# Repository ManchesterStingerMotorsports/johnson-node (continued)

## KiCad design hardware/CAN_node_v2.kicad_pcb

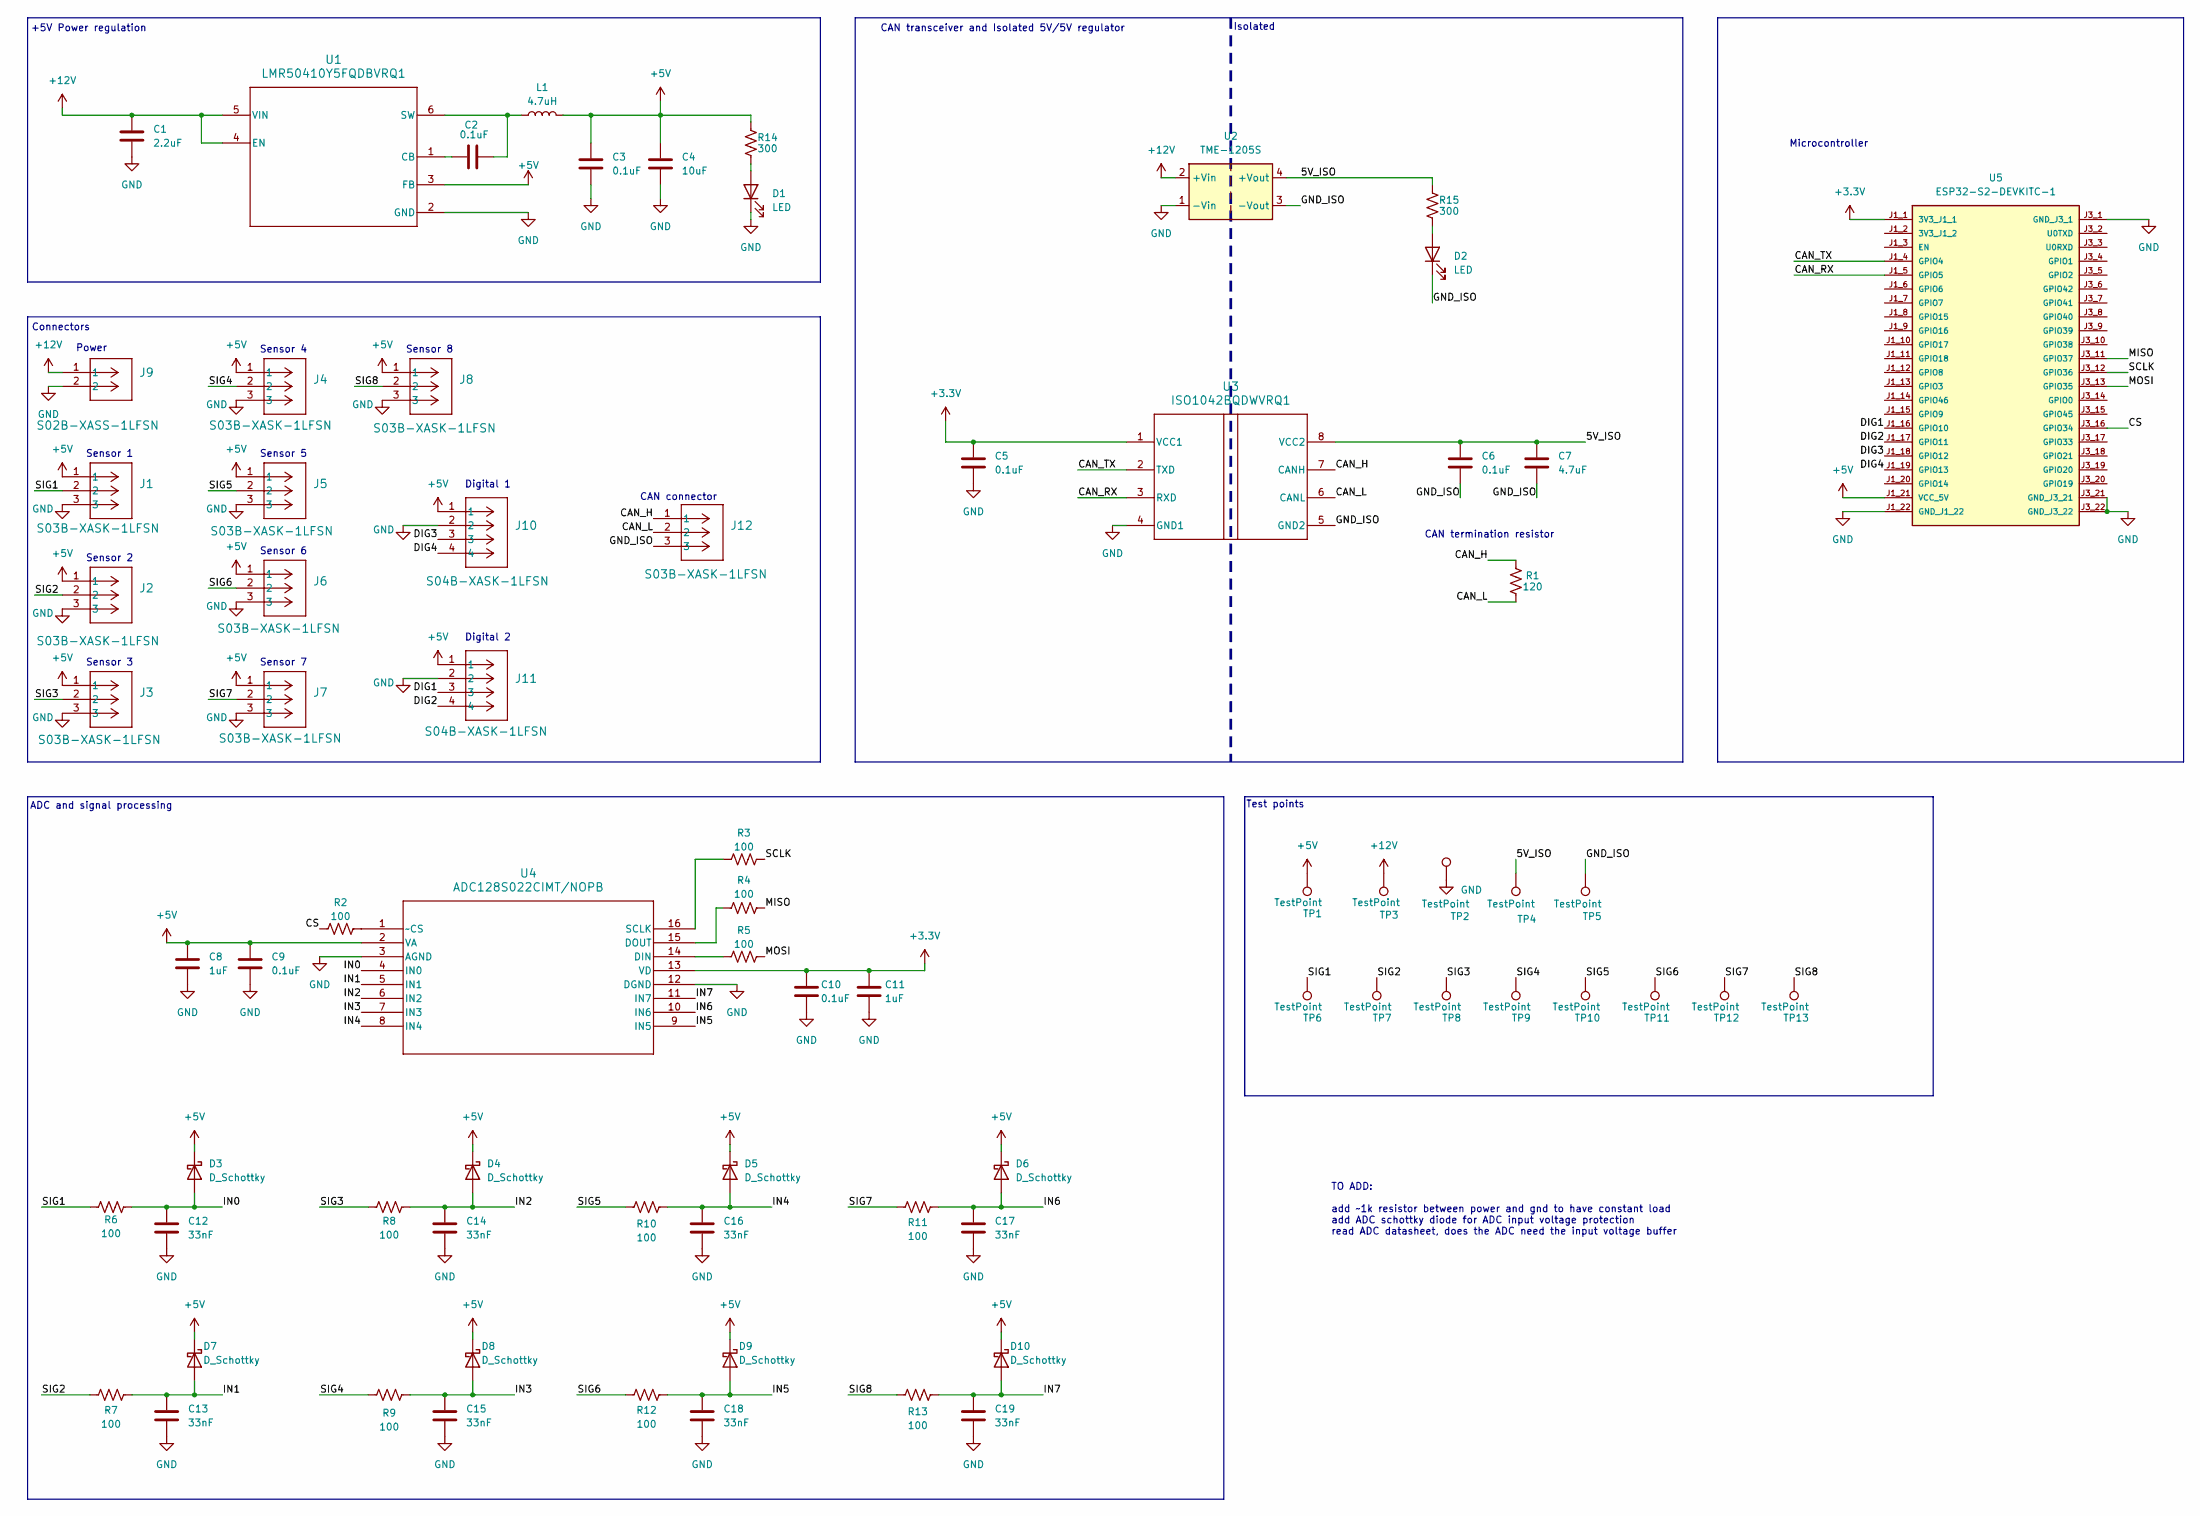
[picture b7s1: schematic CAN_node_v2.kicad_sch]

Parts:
C1: 2.2uF; C_0603_1608Metric_Pad1.08x0.95mm_HandSolder
C2, C3, C5, C6, C9, C10: 0.1uF; C_0603_1608Metric_Pad1.08x0.95mm_HandSolder
C4: 10uF; C_0603_1608Metric_Pad1.08x0.95mm_HandSolder
C7: 4.7uF; C_0603_1608Metric_Pad1.08x0.95mm_HandSolder
C8, C11: 1uF; C_0603_1608Metric_Pad1.08x0.95mm_HandSolder
C12, C13, C14, C15, C16, C17, C18, C19: 33nF; C_0603_1608Metric_Pad1.08x0.95mm_HandSolder
D1, D2: LED; LED_0603_1608Metric_Pad1.05x0.95mm_HandSolder
D3, D4, D5, D6, D7, D8, D9, D10: D_Schottky; LED_0603_1608Metric_Pad1.05x0.95mm_HandSolder
J1, J2, J3, J4, J5, J6, J7, J8, J12: S03B-XASK-1LFSN; CONN_S03B-XASK_JST
J9: S02B-XASS-1LFSN; CONN2_S02B-XASS_295x496_JST
J10, J11: S04B-XASK-1LFSN; CONN_S04B-XASK-1_JST
L1: 4.7uH; L_1008_2520Metric_Pad1.43x2.20mm_HandSolder
R1: 120; R_0603_1608Metric_Pad0.98x0.95mm_HandSolder
R2, R3, R4, R5, R6, R7, R8, R9, R10, R11, R12, R13: 100; R_0603_1608Metric_Pad0.98x0.95mm_HandSolder
R14, R15: 300; R_0603_1608Metric_Pad0.98x0.95mm_HandSolder
TP1, TP2, TP3, TP4, TP5, TP6, TP7, TP8, TP9, TP10, TP11, TP12, TP13: TestPoint; Pin_D0.7mm_L6.5mm_W1.8mm_FlatFork
U1: LMR50410Y5FQDBVRQ1; DBV0006A-MFG
U2: TME-1205S; Converter_DCDC_TRACO_TME_03xxS_05xxS_12xxS_Single_THT
U3: ISO1042BQDWVRQ1; DWV0008A-IPC_A
U4: ADC128S022CIMT/NOPB; ADC128S022
U5: ESP32-S2-DEVKITC-1; MODULE_ESP32-S2-DEVKITC-1; PARTREV 1.0

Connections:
+3.3V: C5.1, C10.1, C11.1, U3.1 (VCC1), U4.13 (VD), U5.J1_1 (3V3_J1_1)
+5V: C3.1, C4.1, C8.1, C9.1, D3.1 (K), D4.1 (K), D5.1 (K), D6.1 (K), D7.1 (K), D8.1 (K), D9.1 (K), D10.1 (K), J1.1, J2.1, J3.1, J4.1, J5.1, J6.1, J7.1, J8.1, J10.1, J11.1, L1.2, R14.1, TP1.1, U1.3 (FB), U4.2 (VA), U5.J1_21 (VCC_5V)
+12V: C1.1, J9.1, TP3.1, U1.4 (EN), U1.5 (VIN), U2.2 (+Vin)
/5V_ISO: C6.1, C7.1, R15.1, TP4.1, U2.4 (+Vout), U3.8 (VCC2)
/CAN_H: J12.1, R1.1, U3.7 (CANH)
/CAN_L: J12.2, R1.2, U3.6 (CANL)
/CAN_RX: U3.3 (RXD), U5.J1_5 (GPIO5)
/CAN_TX: U3.2 (TXD), U5.J1_4 (GPIO4)
/CS: R2.1, U5.J3_16 (GPIO34)
/DIG1: J11.3, U5.J1_16 (GPIO10)
/DIG2: J11.4, U5.J1_17 (GPIO11)
/DIG3: J10.3, U5.J1_18 (GPIO12)
/DIG4: J10.4, U5.J1_19 (GPIO13)
/GND_ISO: C6.2, C7.2, D2.1 (K), J12.3, TP5.1, U2.3 (-Vout), U3.5 (GND2)
/IN0: C12.1, D3.2 (A), R6.2, U4.4 (IN0)
/IN1: C13.1, D7.2 (A), R7.2, U4.5 (IN1)
/IN2: C14.1, D4.2 (A), R8.2, U4.6 (IN2)
/IN3: C15.1, D8.2 (A), R9.2, U4.7 (IN3)
/IN4: C16.1, D5.2 (A), R10.2, U4.8 (IN4)
/IN5: C18.1, D9.2 (A), R12.2, U4.9 (IN5)
/IN6: C17.1, D6.2 (A), R11.2, U4.10 (IN6)
/IN7: C19.1, D10.2 (A), R13.2, U4.11 (IN7)
/MISO: R4.2, U5.J3_11 (GPIO37)
/MOSI: R5.2, U5.J3_13 (GPIO35)
/SCLK: R3.2, U5.J3_12 (GPIO36)
/SIG1: J1.2, R6.1, TP6.1
/SIG2: J2.2, R7.1, TP7.1
/SIG3: J3.2, R8.1, TP8.1
/SIG4: J4.2, R9.1, TP9.1
/SIG5: J5.2, R10.1, TP10.1
/SIG6: J6.2, R12.1, TP11.1
/SIG7: J7.2, R11.1, TP12.1
/SIG8: J8.2, R13.1, TP13.1
GND: C1.2, C3.2, C4.2, C5.2, C8.2, C9.2, C10.2, C11.2, C12.2, C13.2, C14.2, C15.2, C16.2, C17.2, C18.2, C19.2, D1.1 (K), J1.3, J2.3, J3.3, J4.3, J5.3, J6.3, J7.3, J8.3, J9.2, J10.2, J11.2, TP2.1, U1.2 (GND), U2.1 (-Vin), U3.4 (GND1), U4.3 (AGND), U4.12 (DGND), U5.J1_22 (GND_J1_22), U5.J3_1 (GND_J3_1), U5.J3_21 (GND_J3_21), U5.J3_22 (GND_J3_22)
unnamed: D1.2 (A), R14.2
unnamed: D2.2 (A), R15.2
unnamed: C2.1, U1.1 (CB)
unnamed: C2.2, L1.1, U1.6 (SW)
unnamed: R5.1, U4.14 (DIN)
unnamed: R4.1, U4.15 (DOUT)
unnamed: R3.1, U4.16 (SCLK)
unnamed: R2.2, U4.1 (~CS)

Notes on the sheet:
Power
Connectors
Microcontroller
Sensor 2
Sensor 7
Sensor 3
TO ADD: add ~1k resistor between power and gnd to have constant load add ADC schottky diode for ADC input voltage protection read ADC datasheet, does the ADC need the input voltage buffer
Sensor 4
Sensor 6
ADC and signal processing
Sensor 5
CAN transceiver and Isolated 5V/5V regulator
Digital 2
Digital 1
Sensor 8
Test points
Sensor 1
Isolated
+5V Power regulation
CAN connector
CAN termination resistor

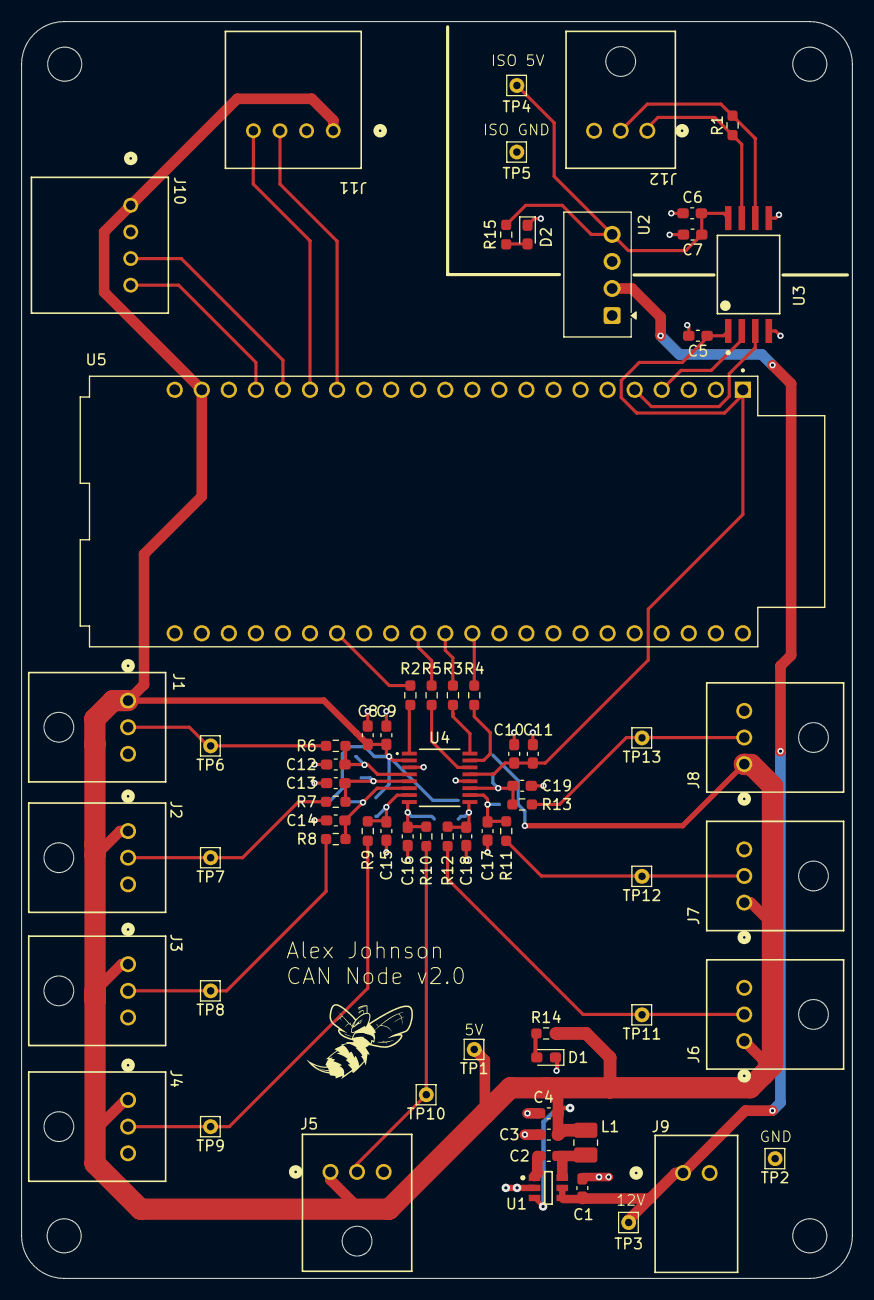
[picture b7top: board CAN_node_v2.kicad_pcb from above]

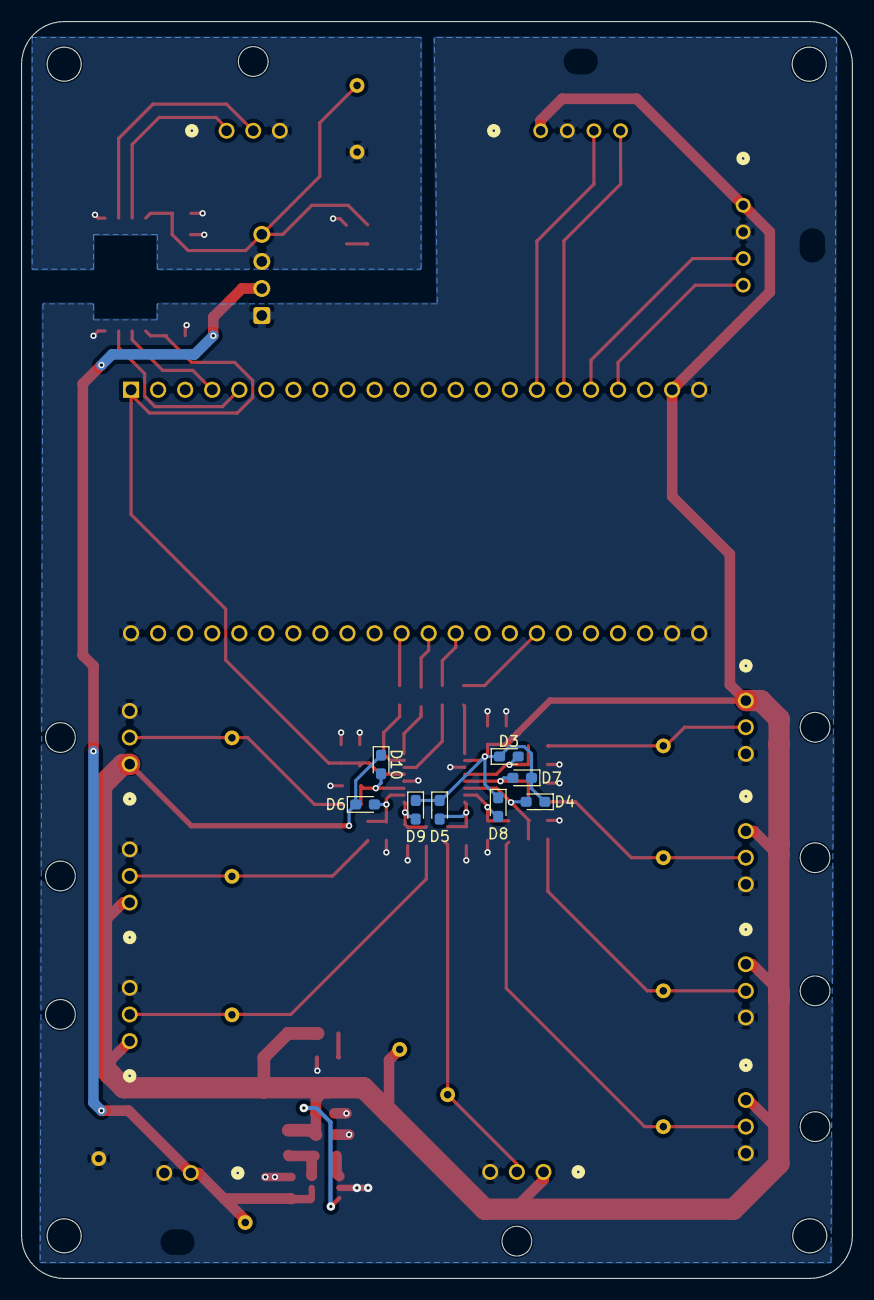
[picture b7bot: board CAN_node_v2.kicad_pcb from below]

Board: 2 copper layers, 78.0 x 118.0 mm, 75 parts (8 on the bottom side), 42 nets.

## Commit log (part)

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2026-04-13 Add ESP hello world example
2026-04-13 gitignore
2026-04-13 code
2026-04-13 Add preliminary hardware
2026-04-13 Update kicad ver
2026-04-14 hello world
2026-04-14 move to c++
2026-04-14 Add MSM_CAN
2026-04-26 clean up and add hats
2026-04-28 hats
2026-05-08 update SGIH
2026-05-12 finish schem
2026-05-13 placement of components
2026-05-14 minor changes
2026-05-14 add onboard reg
2026-05-15 grounding
2026-05-15 3d models
2026-05-15 final ordered version
2026-05-15 README
2026-05-15 johnson glaze
2026-06-17 strain gauge hell
2026-06-17 pull AINBs to 3V3
2026-06-17 change switching reg to adjustable
2026-06-17 add all footprints
2026-06-17 begin rear board
2026-06-17 6 wishbones
2026-06-17 this is worse than torture
2026-06-17 I hate everything and everyone
2026-06-17 connector
2026-06-18 things are looking up
2026-06-18 its finally over
2026-06-20 accelerometer code example
